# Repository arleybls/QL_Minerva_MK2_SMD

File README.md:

# SINCLAIR QL - SMD Minerva MK II - New OS + RTC
SMD clone of the Board of ROM + RTC for Sinclair QL Computer

License under: CERN Open Hardware Licence Version 2 - Strongly Reciprocal

This work is based on Alavaro's Alea Revision that can be found here:
https://github.com/alvaroalea/QL_Minerva_MK2

Please also refer to the original repository and source to find the images for both the GAL and the ROM.

/RTC Tester is a PCF8583 verifier based on arduino nano. Output on serial console. It will help to quickly
sort out broken chips when sourcing.

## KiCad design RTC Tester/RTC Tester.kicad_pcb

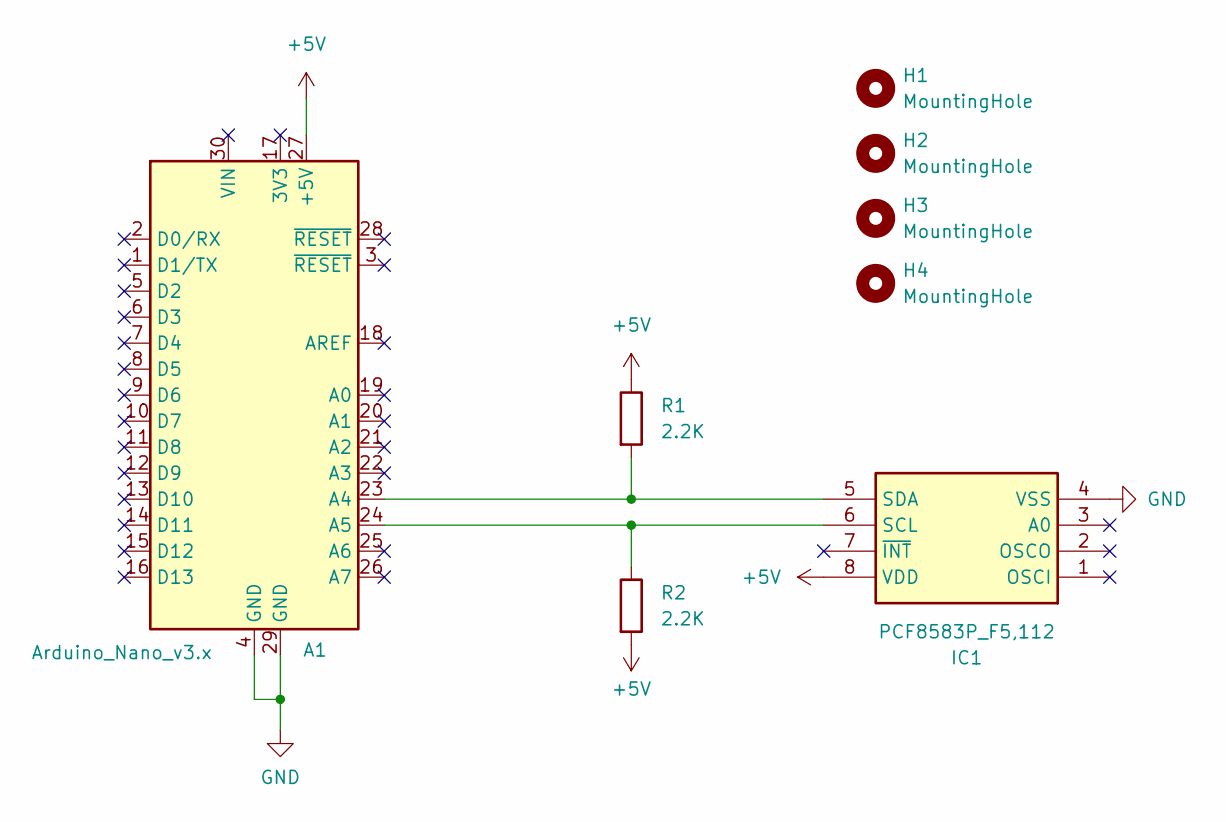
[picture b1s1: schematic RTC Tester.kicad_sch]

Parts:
A1: Arduino_Nano_v3.x; Arduino_Nano
H1, H2, H3, H4: MountingHole; MountingHole_3.2mm_M3
IC1: PCF8583P_F5,112; ZIF16_TO_PCF8583; Mouser Part Number 771-PCF8583PN
R1, R2: 2.2K; R_Axial_DIN0207_L6.3mm_D2.5mm_P10.16mm_Horizontal

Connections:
+5V: A1.27 (+5V), IC1.8 (VDD), R1.1, R2.2
GND: A1.4 (GND), A1.29 (GND), IC1.4 (VSS)
unnamed: A1.23 (A4), IC1.5 (SDA), R1.2
unnamed: A1.24 (A5), IC1.6 (SCL), R2.1

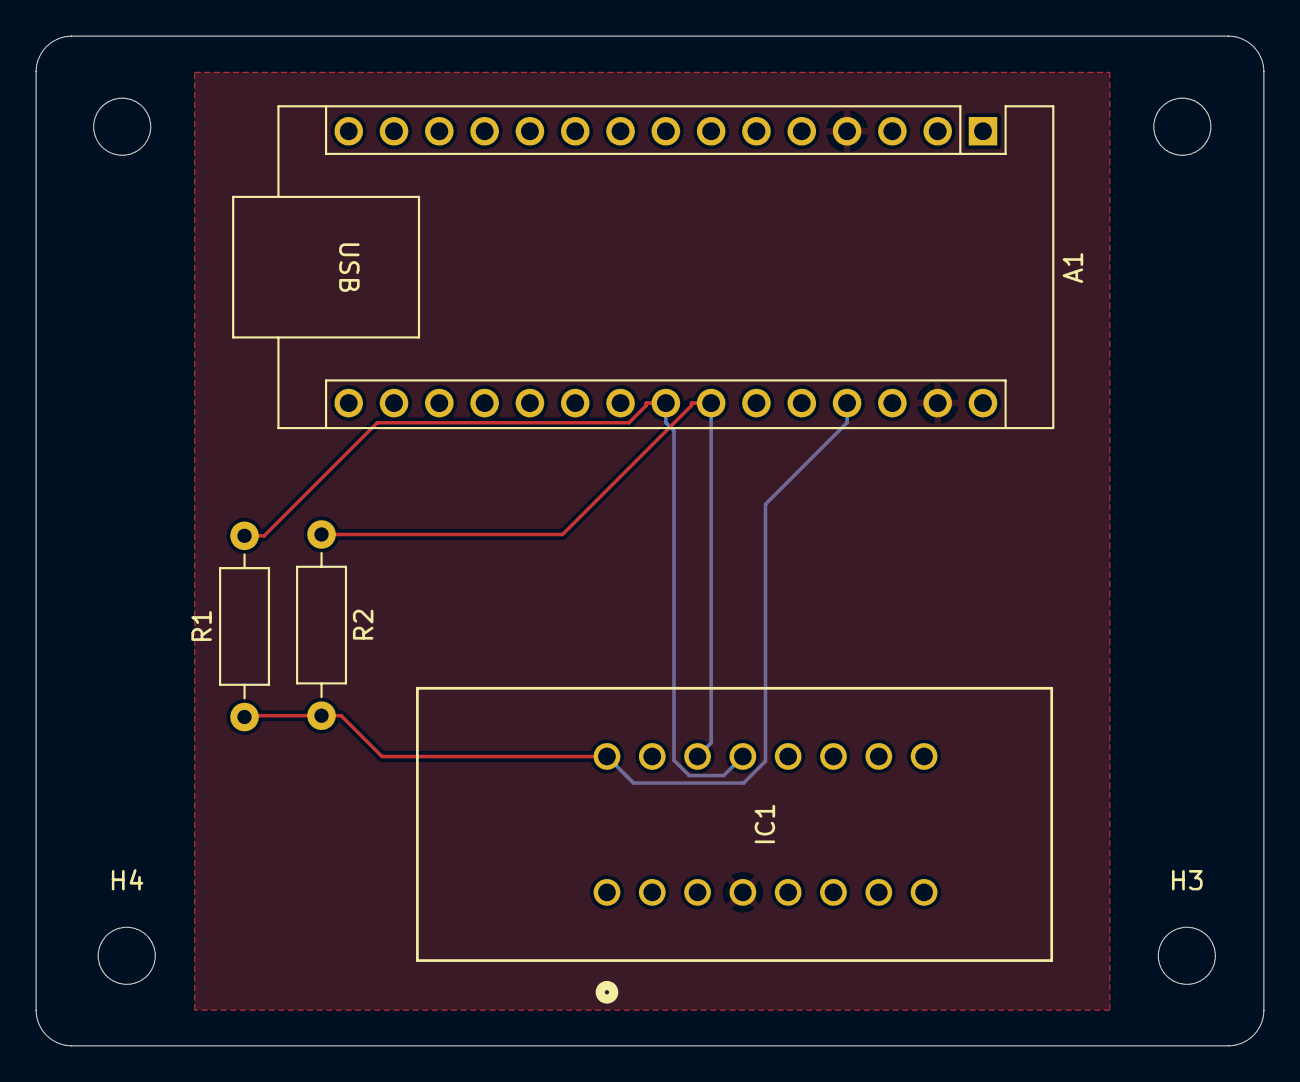
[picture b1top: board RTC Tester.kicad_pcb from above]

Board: 2 copper layers, 68.8 x 56.6 mm, 8 parts (0 on the bottom side), 4 nets.

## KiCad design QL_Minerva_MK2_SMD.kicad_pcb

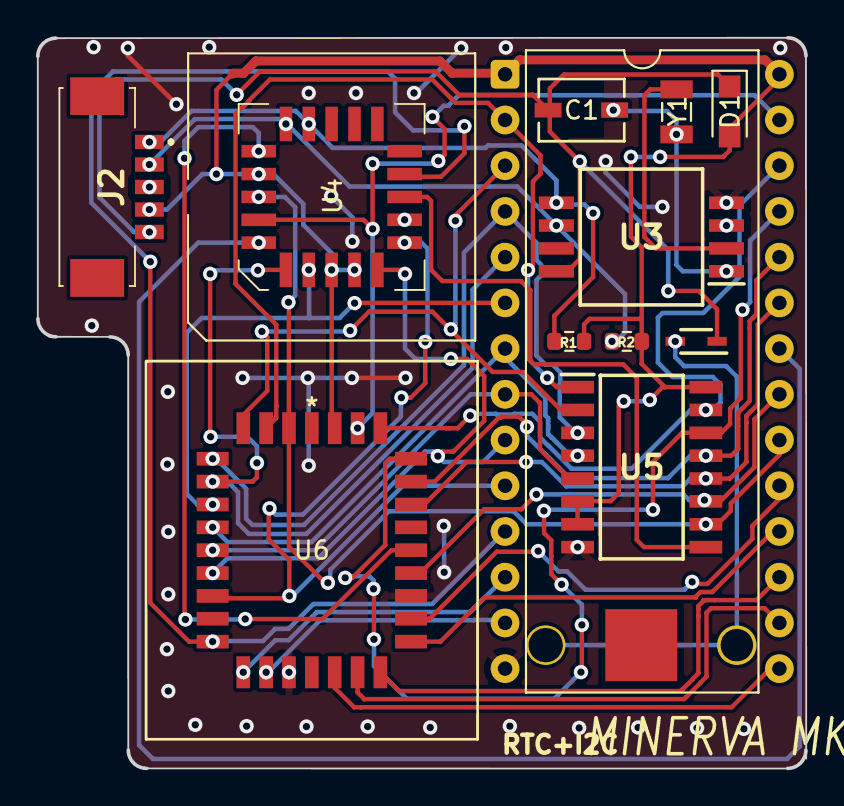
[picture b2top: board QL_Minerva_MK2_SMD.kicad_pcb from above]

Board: 2 copper layers, 42.7 x 40.6 mm, 13 parts (0 on the bottom side), 35 nets.

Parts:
C1: 30p Variable; TZC3_MUR
D1: BAT42; Nexperia_CFP3_SOD-123W
D2: BAT42; BAT42WS
J1: Conn_01x02_Pin; CR927Holder
J2: Conn_01x05_Pin; PicoBlade_53261
R1, R2: 2K2; R_0603_1608Metric
U1: Socket to QL; DIP-28_W15.24mm
U3: PCF8583P; PCF8583T
U4: GAL16V8; PLCC-20_SMD-Socket
U5: 74LS133; SN74ALS133NSR
U6: 27C512PLCC; CONN_PLCC-32-AT-SMT_ADM
Y1: 32.768 kHz; XTAL_FC-135_32.7680KA-A0

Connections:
+5V: D1.2 (A), J2.4, R1.1, R2.1, U1.1 (A15), U1.28 (VCC), U4.6 (I6), U4.7 (I7), U4.20 (VCC), U5.6, U5.7, U5.16 (VCC), U6.32 (VCC)
/A0: U1.10 (A0), U4.9 (I9), U6.11 (A0)
/A1: U1.9 (A1), U4.8 (I8), U6.10 (A1)
/A2: U1.8 (A2), U5.5, U6.9 (A2)
/A3: U1.7 (A3), U5.4, U6.8 (A3)
/A4: U1.6 (A4), U4.5 (I5), U6.7 (A4)
/A5: U1.5 (A5), U4.4 (I4), U6.6 (A5)
/A6: U1.4 (A6), U5.3, U6.5 (A6)
/A7: U1.3 (A7), U5.2, U6.4 (A7)
/A8: U1.25 (A8), U5.14, U6.29 (A8)
/A9: U1.24 (A9), U5.13, U6.28 (A9)
/A10: U1.21 (A10), U5.11, U6.24 (A10)
/A11: U1.23 (A11), U5.12, U6.27 (A11)
/A12: U1.2 (A12), U5.1, U6.3 (A12)
/A13: U1.26 (A13), U5.15, U6.30 (A13)
/A14: U1.27 (A14), U4.2 (I2), U6.31 (A14)
/A15: U1.20 (~CE), U4.1 (I1/CLK), U5.10, U6.2 (A15)
/D0: U1.11 (D0), U4.12 (IO8), U6.13 (O0)
/D1: U1.12 (D1), U6.14 (O1)
/D2: U1.13 (D2), U6.15 (O2)
/D3: U1.15 (D3), U6.18 (O3)
/D4: U1.16 (D4), U6.19 (O4)
/D5: U1.17 (D5), U6.20 (O5)
/D6: U1.18 (D6), U6.21 (O6)
/D7: U1.19 (D7), U6.22 (O7)
/DECODE: U4.11 (I10/~OE), U5.9
/IC_ROMOE: U4.19 (IO1), U6.25 (~OE/VPP)
/K: C1.1, D1.1 (K), D2.1 (K), J2.5, U3.8 (Vdd)
/QL_ROMOE: U1.22 (~OE/Vpp), U4.3 (I3)
/SCL: J2.2, R2.2, U3.6 (SCL), U4.18 (IO2)
/SDA: J2.1, R1.2, U3.5 (SDA), U4.17 (I03)
GND: J1.2, J2.3, U1.14 (GND), U3.3 (A0), U3.4 (Vss), U4.10 (GND), U5.8 (GND), U6.16 (GND), U6.23 (~CE)
unnamed: D2.2 (A), J1.1
unnamed: C1.2, U3.1 (OSCI), Y1.1
unnamed: U3.2 (OSCO), Y1.2

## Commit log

2025-11-02 Update README with license and source references
    Added licensing information and references to original work.
2025-11-02 Main files
    Added main files
2025-11-02 Correct coments
2025-11-02 RTC Tester
    RTC Tester
2025-11-02 Update README with RTC Tester details
    Added description for RTC Tester functionality.
2025-11-02 Add image to README for RTC Tester
    Added an image to the README for better visualization.
2025-11-02 Fix typo in README regarding Alea Revision
